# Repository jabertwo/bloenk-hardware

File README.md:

Blönk USB Notifier
=========
Schematics, PCB Layout and Windows Drivers

About
--
Blönk is an universal RGB light attached to the USB port. Originally designt as notifier for the Microsoft Lync software, Blönk now can be used for many other applications.

Flexibility
--
You can ether integrate Blönk into your own projects by using the .NET Library (or commandline software) or you can use Blönk with the already build software as Microsoft Lync notifier.

Software
--
You can find the sourcecode for the .NET library and software (also Lync integration) in a separate repository: https://github.com/johannes85/bloenk-software  
I also published more details about the project on my YouTube channel and website (in German): 
http://www.domestichacks.info/projekte/bloenk-usb-licht-fuer-lync/  
https://www.youtube.com/domestichacks

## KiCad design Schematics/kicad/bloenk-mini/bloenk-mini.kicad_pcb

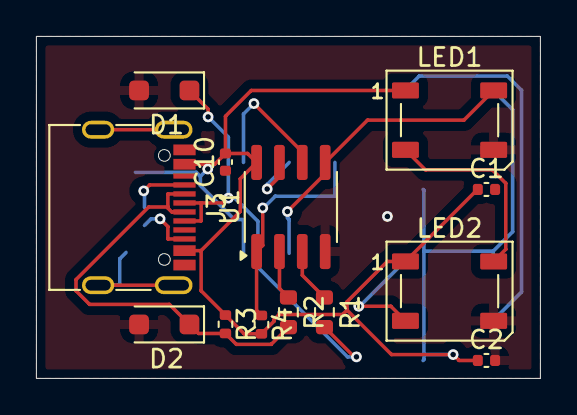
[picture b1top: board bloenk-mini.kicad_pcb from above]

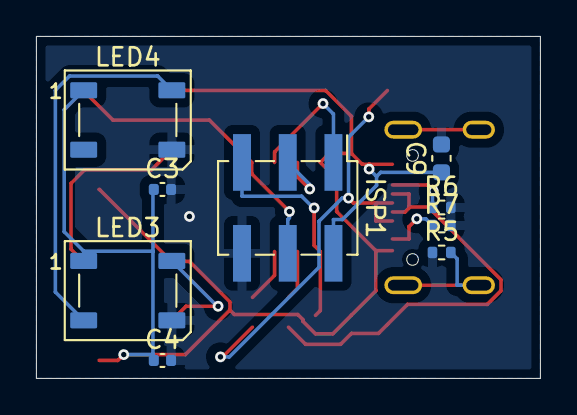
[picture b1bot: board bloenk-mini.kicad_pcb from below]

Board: 2 copper layers, 28.0 x 19.0 mm, 22 parts (9 on the bottom side), 16 nets.

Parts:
C1, C2, C3, C4, C10: 100n; C_0402_1005Metric
C9: 10µF; C_0603_1608Metric
D1, D2: 3V6; D_SOD-123F
ISP1: AVRISP-6; PinHeader_2x03_P2.54mm_Vertical_SMD
J3: USB_C_Receptacle_USB2.0_16P; USB_C_Receptacle_G-Switch_GT-USB-7010ASV
LED1, LED2, LED3, LED4: WS2812B; LED_WS2812B_PLCC4_5.0x5.0mm_P3.2mm
R1, R2: 75; R_0603_1608Metric
R3: 1.5K; R_0402_1005Metric
R4: 10K; R_0402_1005Metric
R5: 1M; R_0402_1005Metric
R6, R7: 5.11k; R_0402_1005Metric
U1: ATTINY85; SOIC-8_3.9x4.9mm_P1.27mm

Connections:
/D+: D1.1, J3.A6 (D+), J3.B6 (D+), R1.2
/D-: D2.1, J3.A7 (D-), J3.B7 (D-), R2.2, R3.2
/PB0: ISP1.4 (MOSI), LED1.4, U1.5 (PB0)
/PB1: ISP1.1 (MISO), U1.6 (PB1)
/PB2: ISP1.3 (SCK), U1.7 (PB2)
/PB3: R2.1, U1.2 (PB3)
/PB4: R1.1, U1.3 (PB4)
/RST: ISP1.5 (RST), R4.1, U1.1 (PB5)
GND: C1.2, C2.2, C3.2, C4.2, C9.2, C10.1, D1.2, D2.2, ISP1.6 (GND), J3.A1 (GND), J3.A12 (GND), J3.B1 (GND), J3.B12 (GND), LED1.3, LED2.3, LED3.3, LED4.3, R5.1, R6.2, R7.2, U1.4 (GND)
unnamed: J3.A5 (CC1), R6.1
unnamed: J3.B5 (CC2), R7.1
unnamed: J3.S1 (SHIELD), R5.2
VCC: C1.1, C2.1, C3.1, C4.1, C9.1, C10.2, ISP1.2 (VCC), J3.A4 (VBUS), J3.A9 (VBUS), J3.B4 (VBUS), J3.B9 (VBUS), LED1.1, LED2.1, LED3.1, LED4.1, R3.1, R4.2, U1.8 (VCC)
WS-1: LED1.2, LED2.4
WS-2: LED2.2, LED3.4
WS-3: LED3.2, LED4.4

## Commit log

2014-06-24 Initial release
2014-06-24 Moved license file for the hardware Added readme
2025-03-05 WIP new kicad version of pcb with usb type c
